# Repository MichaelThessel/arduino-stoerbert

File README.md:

# Intro

This repository contains the files required to build an easy to use MP3 player for small children.
This project is heavily inspired by [Hoerbert](https://en.hoerbert.com).

Main components required to build:

* Arduino Uno
* Adafruit Music Maker shield
* Speaker
* Button PCB (see below)
* Volume Pot
* On/Off switch
* Battery holders
* Hookup wire

# Button PCB schematics

I created a custom PCB for the input buttons. The schematics for that are in the
cad directory in KiCad format. The Arduino UNO does not have enough GPIO pins
for the Music Maker shield, the volume pot, and 12 buttons. To reduce the amount
of GPIO pins required for the buttons I used 2 shift registers. That reduces the
amount of required pins for the buttons to 3.

I used the following components:

* [2x CD4021BC shift registers](http://www.redrok.com/CMOS_CD4021BC_8-StageStaticShiftRegister_Fairchild.pdf)
* [OmronB3F Buttons](https://www.amazon.ca/gp/product/B07CW1XJTS)
* as well as some 0805 1k resistors

If you want to etch the PCB yourself you can print this PDF on a transparency.
Make sure to use US letter sized transparencies if you use the PDF below.
Alternatively you can just create a new PDF from the KiCad layout.

[PCB transparency](/assets/pcb_cad.pdf)

I followed this [PCB etching process](https://www.youtube.com/watch?v=tWnfnt2rNO0)

# Button layout

## Regular mode

    [album 1]   [album 2]       [album 3]
    [album 4]   [album 5]       [album 6]
    [album 7]   [album 8]       [album 9]
    [prev]      [play_pause]    [next]

## God mode

    [1]         [2]             [3]
    [4]         [5]             [6]
    [7]         [8]             [9]
    [0]         [play_pause]    [next]

# God mode

The player supports 2 different modes. Regular mode and god mode.
In regular mode one album is assigned to each button. This is the default mode
and what the device is mainly intended for.
To add more functionality, god mode has been added. This mode allows to add an
alternative set of albums which makes it a handy MP3 player for parents as well.
In that mode instead of directly playing an album for each button press, the
buttons act as numerical input buttons. 2 buttons have to be pressed to select
an album. I.e. 4 - 2 to select album 42. Up to 99 albums are supported in
god mode.

To enter god mode the god mode sequence has to be pressed. The god mode sequence
is: prev - play_pause - play_ pause - next (regular mode keyboard layout). The
same sequence can be used to switch back to regular mode. When the sequence has
been entered correctly a short beep will sound.

# SD card

## Structure

The SD card needs to be formated with FAT32.

The root folder structure needs to be:

k01 ... k09 for the regular albums and

g01 ... g99 for the god mode albums

The files in each folder need to be named:

01.mp3 ... 99.mp3

i.e.

    /k06/01.mp3
    /k06/02.mp3
    /k06/03.mp3
    /k06/04.mp3
    /k06/05.mp3
    /k06/06.mp3

## Convert files to supported file format

    a=`find ./ -type f -name "*.mp3" | awk '{print "mv", "\""$0"\"", substr($0, 3, 2)".mp3;"}'`; eval $a

This only works if the files are named with the first 2 digits indicating their
track name already. I.e. `01-meshuggah-bleed.mp3`. A great alternative for batch
renaming the files is [Mp3Tag](https://www.mp3tag.de/en).

# Auto resume

The player will automatically resume the last played track after power off (if
powered off before an album finished playing).

# Power saving

To remind the user to turn of the device once the album has finished playing the
player will sound a short beep every 5 minutes once the last album has played.

# Mono mode

To keep the player compact and reduce power consumption this has been designed
to work with a single speaker. The Music Maker shield is configured to work in
mono mode. You can connect your speaker to either of the 2 speaker ports. In
case you want to build a stereo version you can simply remove these lines from
player.cpp

    // Enable mono mode
    vs1053.sciWrite(VS1053_REG_WRAMADDR, 0x1e09);
    vs1053.sciWrite(VS1053_REG_WRAM, 0x0001);

# Case build

I added an album of the full build on [Imgur](https://imgur.com/gallery/S2kZkn8)

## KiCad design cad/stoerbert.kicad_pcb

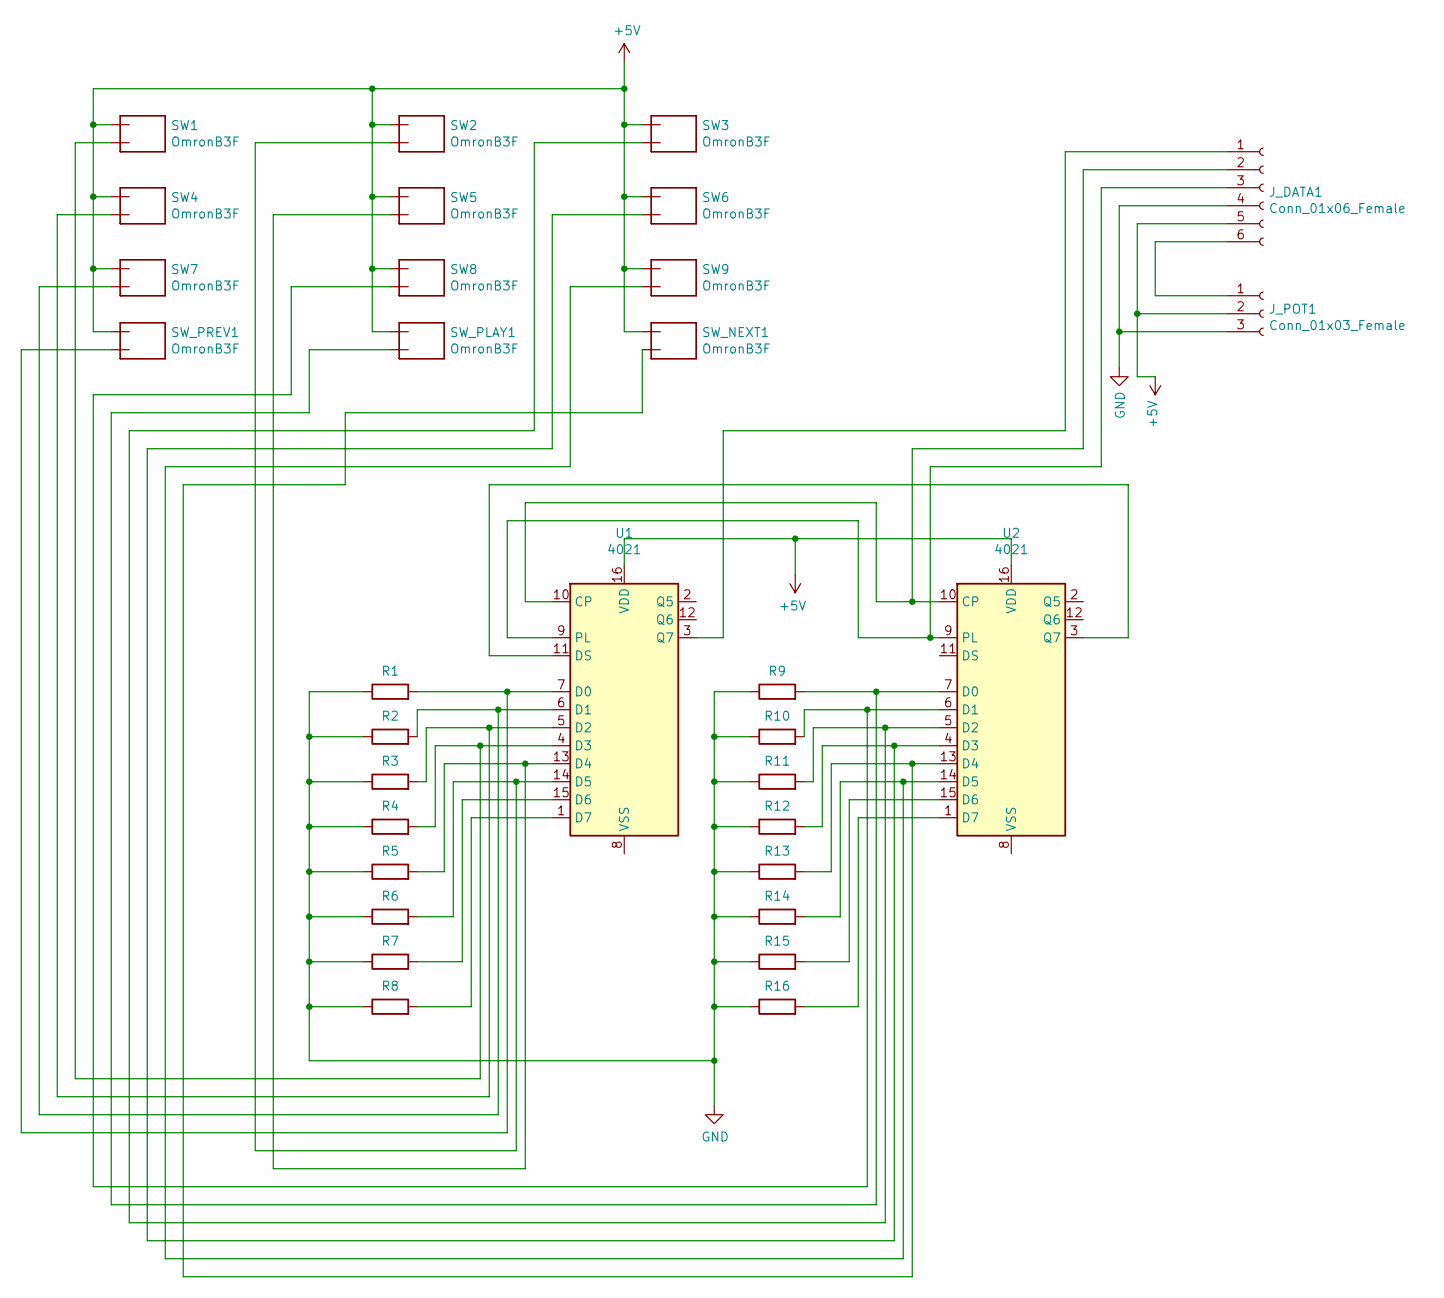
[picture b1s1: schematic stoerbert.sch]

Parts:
J_DATA1: Conn_01x06_Female; PinHeader_1x06_P2.00mm_Vertical
J_POT1: Conn_01x03_Female; PinHeader_1x03_P2.00mm_Vertical
R1: 1K; R_0805_2012Metric_Pad1.15x1.40mm_HandSolder
R2, R3: 1k; R_0805_2012Metric_Pad1.15x1.40mm_HandSolder
R4, R5, R6, R7, R8, R9, R10, R11, R12, R13, R14, R15, R16: R; R_0805_2012Metric_Pad1.15x1.40mm_HandSolder
SW1, SW2, SW3, SW4, SW5, SW6, SW7, SW8, SW9: OmronB3F; ToggleSwitch
SW_NEXT1: OmronB3F; ToggleSwitch
SW_PLAY1: OmronB3F; ToggleSwitch
SW_PREV1: OmronB3F; ToggleSwitch
U1, U2: 4021; DIP-16_W7.62mm_large

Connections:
+5V: J_DATA1.5, J_POT1.2, SW1.1, SW2.1, SW3.1, SW4.1, SW5.1, SW6.1, SW7.1, SW8.1, SW9.1, SW_NEXT1.1, SW_PLAY1.1, SW_PREV1.1, U1.16 (VDD), U2.16 (VDD)
GND: J_DATA1.4, J_POT1.3, R1.1, R2.1, R3.1, R4.1, R5.1, R6.1, R7.1, R8.1, R9.1, R10.1, R11.1, R12.1, R13.1, R14.1, R15.1, R16.1
unnamed: J_DATA1.1, U1.3 (Q7)
unnamed: J_DATA1.2, U1.10 (CP), U2.10 (CP)
unnamed: J_DATA1.3, U1.9 (PL), U2.9 (PL)
unnamed: J_DATA1.6, J_POT1.1
unnamed: R1.2, SW_PREV1.3, U1.7 (D0)
unnamed: R2.2, SW7.3, U1.6 (D1)
unnamed: R3.2, SW4.3, U1.5 (D2)
unnamed: R4.2, SW1.3, U1.4 (D3)
unnamed: R5.2, SW5.3, U1.13 (D4)
unnamed: R6.2, SW2.3, U1.14 (D5)
unnamed: R7.2, U1.15 (D6)
unnamed: R8.2, U1.1 (D7)
unnamed: R9.2, SW_PLAY1.3, U2.7 (D0)
unnamed: R10.2, SW8.3, U2.6 (D1)
unnamed: R11.2, SW3.3, U2.5 (D2)
unnamed: R12.2, SW6.3, U2.4 (D3)
unnamed: R13.2, SW_NEXT1.3, U2.13 (D4)
unnamed: R14.2, SW9.3, U2.14 (D5)
unnamed: R15.2, U2.15 (D6)
unnamed: R16.2, U2.1 (D7)
unnamed: U1.11 (DS), U2.3 (Q7)

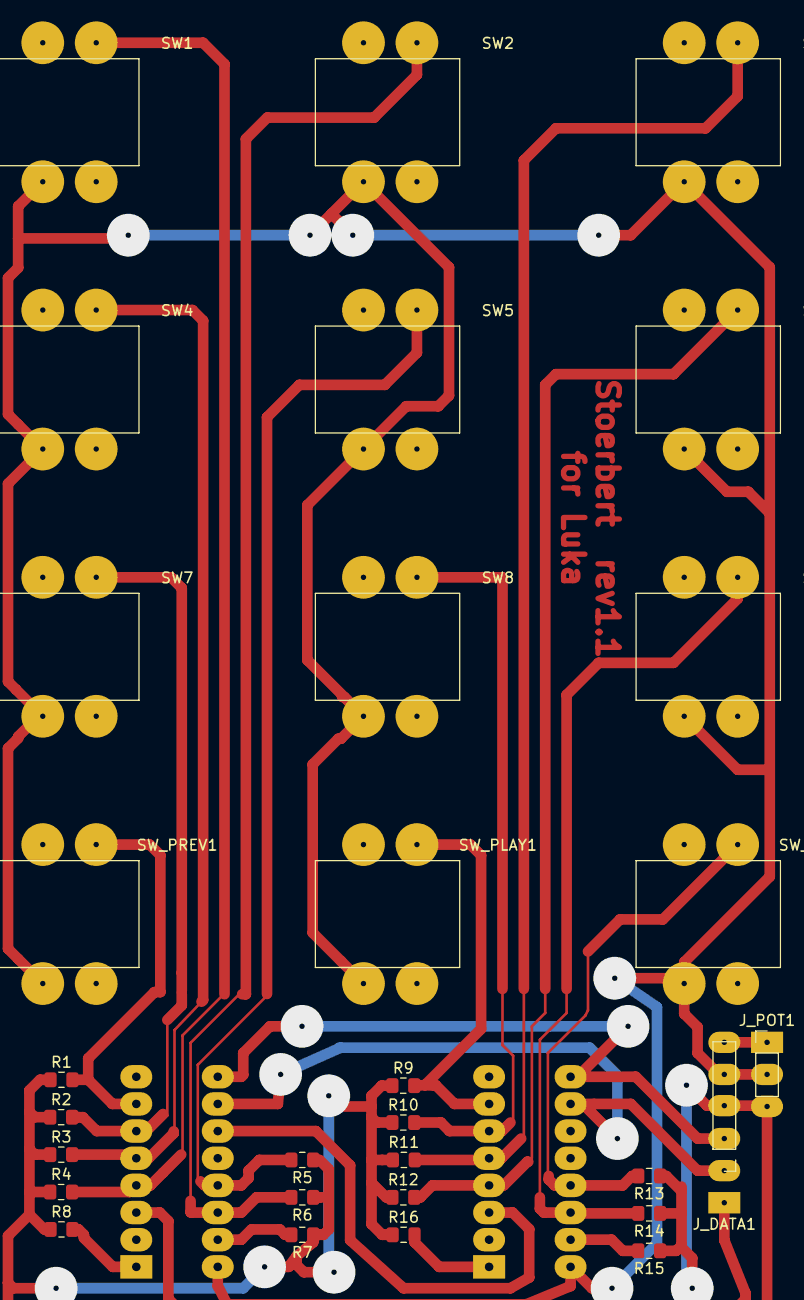
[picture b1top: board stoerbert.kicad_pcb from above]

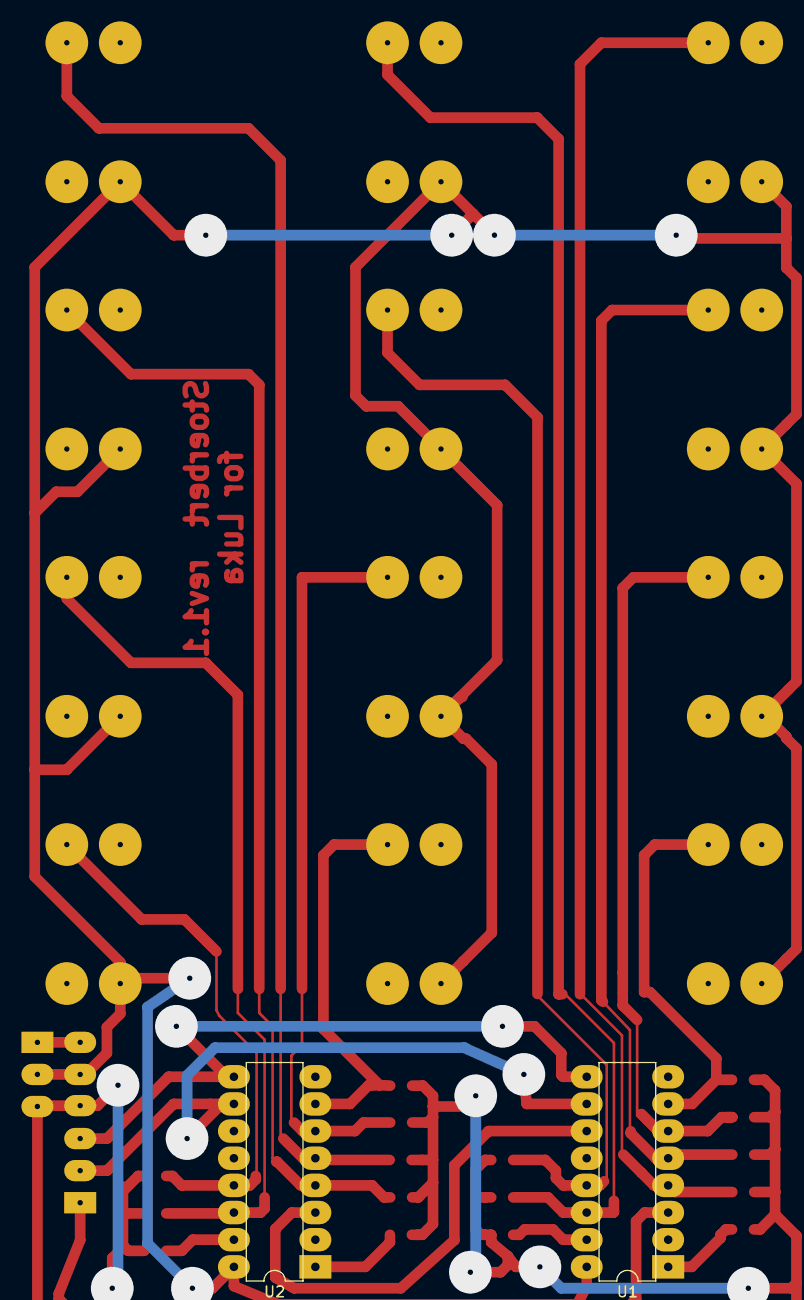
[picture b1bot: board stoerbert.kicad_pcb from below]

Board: 2 copper layers, 32 parts (2 on the bottom side), 23 nets.

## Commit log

2019-11-08 Implemented prev next
2019-11-08 Added god mode
2019-11-08 Added MP3 file name validation
2019-11-19 Added TODOs
2019-11-19 Log invalid commands
2019-11-19 Added god mode sequence
2019-11-24 Added TODO
2019-11-24 Don't start playing album if album is empty
2019-11-24 Corrected album track counting
2019-11-24 Added god mode chime
2019-11-24 Added automatic album advancing
2019-11-24 Made god mode a toggle
2019-11-26 Added volume pot handling
2019-11-26 Added support for button shift registers
2019-11-27 Added button debouncing
2019-11-27 Added comments
2019-11-27 Improved volume mapping
2019-11-27 Added shift register mappings
2019-11-27 Improved shift register variables
2019-11-27 Optimized player variables
2019-11-27 Added PCB project files
2019-11-29 Fixed debounce delay overflow
2019-11-29 Improved command handling
2019-11-29 Finalized button handling
2019-11-30 Moved pin and debug definitions to header files
2019-11-30 Moved shift register handling to seperate files
2019-11-30 Moved player to dedicated file
2019-11-30 Fixed debounce bug
2019-11-30 Reduced god mode chime time
2019-11-30 Added file sorting
2019-11-30 Improved player stability
2019-12-02 Added power saving settings
2019-12-03 Fixed button mapping
2019-12-04 Fixed access to uninitialized musicPlayer
2019-12-08 Fixed volume control
2019-12-08 Added PCB design files
2019-12-09 Added resume functionality
2019-12-09 Updated todo
2019-12-11 Added power reminder
2019-12-16 Updated PCB
2019-12-17 Changed button assignments
2019-12-17 Added file conversion command
2019-12-17 Reset playback before loading album
2019-12-18 Added watchdog
2019-12-18 Changed god mode sequence
2019-12-18 Implemented god mode album select
2019-12-18 Added readme
2019-12-18 Formatting fixes
2019-12-18 Added power saving section
2019-12-18 Added image assets
2019-12-18 Fixed typo
2019-12-18 Restructured readme
2019-12-18 Fixed link
2019-12-19 Added VS1053 patches
2019-12-19 Added mono mode
2019-12-19 Disable VS1053 ADC
2019-12-26 Added photos
2020-01-22 Added pinout diagram
2020-01-22 Fixed error in comment
2020-02-07 Fixed reset lopp when EEPROM has no valid state
